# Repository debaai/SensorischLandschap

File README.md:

# Sensorisch Landschap
Public github repository for the project Sensorisch Landschap. In this project we desinged and build measurement stations for measuring soil moisture, soil temperature, humidity, temperature and atmospheric CO2 on grasslands. This repository contains all firmware and hardware designs developed during this project. More information about the project can be found on www.sensorischlandschap.nl

## Sensors
The 'sensors' folder contains firmware and hardware developed in this project. 
 The main components used for the measurement station are:
- Meet Je Stad PCB Proto v4 
- Pinotech Soilwatch 10
- Si7021 temperature and humidity sensor
- Sensirion SDC30 CO2 sensor

The Meet Je Stad PCB is responsible for reading the sensors and transmitting the data using the LoRaWAN protocol. The firmware provided in the sensors folder is forked from the original Meet Je Stad firmware (https://github.com/meetjestad/mjs_firmware), with various (major) alterations in the code. Additionally a custom wakeup timer was designed to prevent the PCB to jam. This folder contains both the electronic schematics as well as the firmware for this add-on device.

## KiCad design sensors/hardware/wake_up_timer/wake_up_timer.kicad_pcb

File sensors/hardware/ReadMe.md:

# SensorischLandschap - Sensors - Hardware

## MJS_2020_proto_v4
The Meet Je Stad MJS2020 PCB (proto_v4) was used to perform data collection from the sensors and transmission over LoRa. 
This PCB is open Hardware and the design files and license information can be found on the MJS2020 branch of the mjs_pcb repository of Meet Je Stad: 
https://github.com/meetjestad/mjs_pcb/tree/MJS2020

## wake_up_timer
PCB design files for the external watchdog / wake up timer add-on for the MJS2020 PCB. The PCB is designed in KiCad, which is Open Source software and can be downloaded from https://kicad.org/

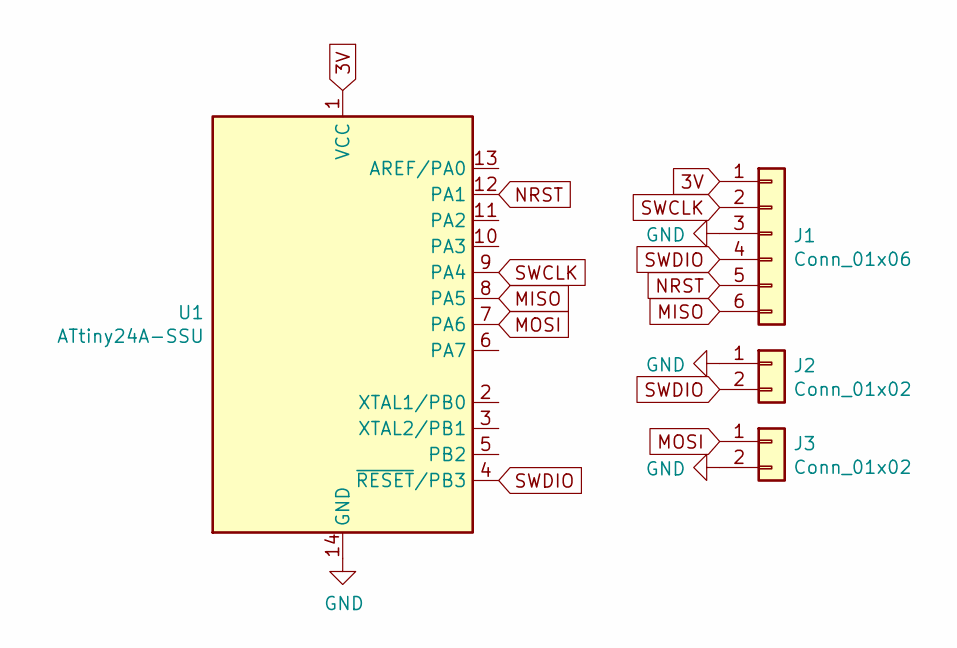
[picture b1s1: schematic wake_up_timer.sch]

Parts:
J1: Conn_01x06; PinHeader_1x06_P2.54mm_Vertical
J2, J3: Conn_01x02; PinHeader_1x02_P2.54mm_Vertical
U1: ATtiny24A-SSU; SOIC-14_3.9x8.7mm_P1.27mm

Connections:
3V: J1.1, U1.1 (VCC)
GND: J1.3, J2.1, J3.2, U1.14 (GND)
MISO: J1.6, U1.8 (PA5)
MOSI: J3.1, U1.7 (PA6)
NRST: J1.5, U1.12 (PA1)
SWCLK: J1.2, U1.9 (PA4)
SWDIO: J1.4, J2.2, U1.4 (~RESET~/PB3)

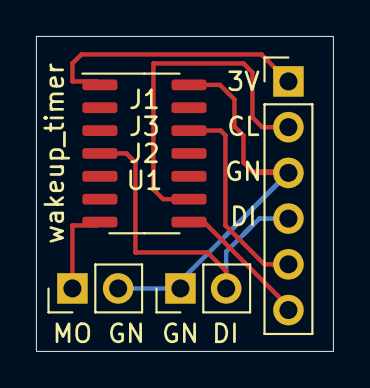
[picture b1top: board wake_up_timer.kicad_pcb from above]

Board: 2 copper layers, 16.5 x 17.5 mm, 4 parts (0 on the bottom side), 7 nets.

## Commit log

2023-01-26 sensor firmware and hardware added and all folders provided with a ReadMe file'
2023-01-26 Copyright information provided
2023-01-26 Update README.md
    Added reference to website
2023-10-31 Update README.md
    typo
2023-10-31 removed empty analysis and dataset folders
2023-10-31 Update README.md
    More information added
2023-10-31 Update README.md
    Components of the setup added
2023-10-31 Update README.md
    small change
